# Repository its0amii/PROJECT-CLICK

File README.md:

PROJECT-CLICK

PROJECT-CLICK is a **3×2 matrix macropad** with a **cyberpunk-inspired design**, built around the **XIAO RP2040**.
I tried to make it look good as posible and it was my first build so it will have its own problems
(the case is tight fit)

## Features
3x2 matrix 
multilayered keys
knob for volume 
display

## Hackpad Overview

> *Screenshot build*

## Schematic

The schematic includes:

* 6-key matrix with individual diodes
* OLED display connection
* Rotary encoder
* RP2040-based controller

Designed using **KiCad**.

> *Screenshot of the schematic*

## PCB

I used KiCad to design my PCB and used JLCPCB to get it printed

* Cherry MX switch 

> *PCBlayout*

## Case & Assembly

the case have two part top and bottom 

* Base (holds the PCB)
* Top plate 

scrwe used in this project is **M3 screws and heatset inserts**

> *Screenshot of the case and how it fits together*

## Firmware Overview

PROJECT-CLICK is designed to run **KMK firmware**.

Planned functionality:

* 6 programmable macro keys
* Rotary encoder for volume/scrolling/custom actions(such as multilayering)
* OLED display for status and layers.

(program is not perfect or tested yet since i am new to this )

## Bill of Materials

Everything required to build one PROJECT-CLICK unit:

### Electronics

* 6× Cherry MX switches
* 6× Blank DSA keycaps
* 6× 1N4148 DO-35 diodes
* 1× 0.91" 128×32 OLED display
* 1× EC11 rotary encoder
* 1× XIAO RP2040

### Hardware

* 10× M3×5×4 heatset inserts
* 15× M3×16mm screws

### Case

* 1× Case (2 printed parts)

## Tools Used

* **KiCad**
* **Fusion 360**
* **KMK** 
* **3D Printer**

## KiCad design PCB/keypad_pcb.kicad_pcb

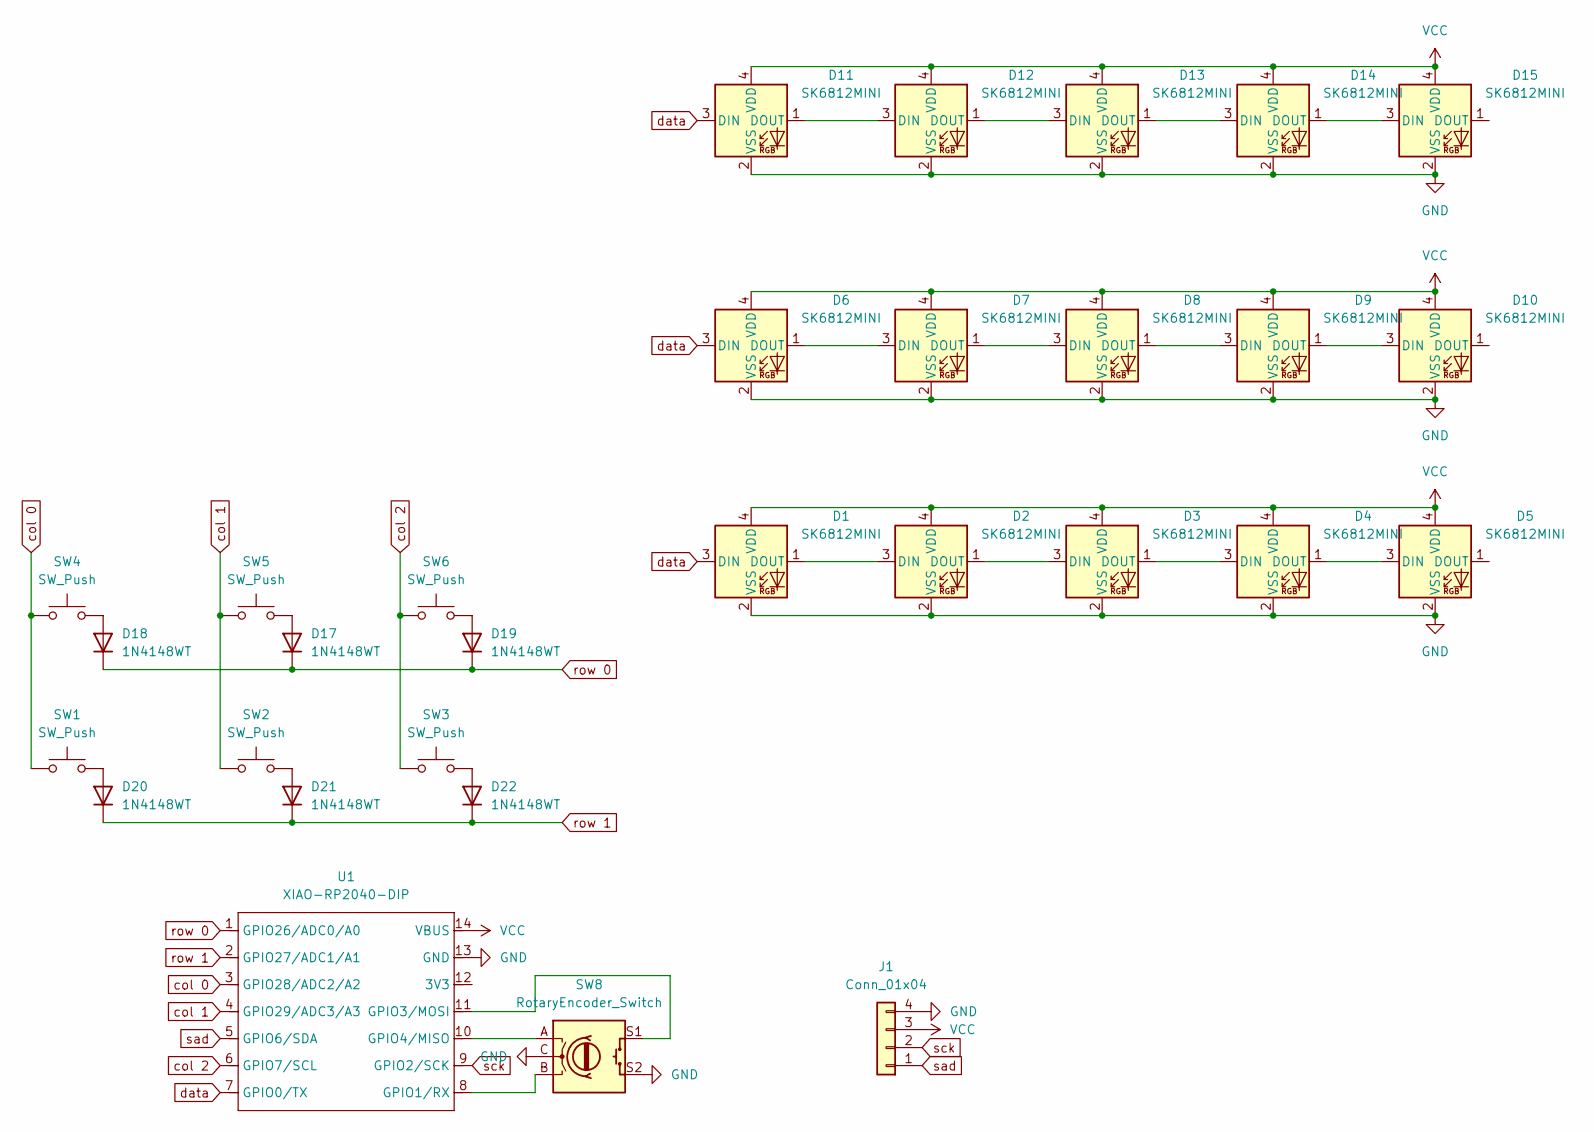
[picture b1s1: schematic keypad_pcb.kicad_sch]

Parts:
D1, D2, D3, D4, D5, D6, D7, D8, D9, D10, D11, D12, D13, D14, D15: SK6812MINI; LED_SK6812MINI_PLCC4_3.5x3.5mm_P1.75mm
D17, D18, D19, D20, D21, D22: 1N4148WT; Diode_DO-35
J1: Conn_01x04; OLED_128x32
SW1, SW2, SW3, SW4, SW5, SW6: SW_Push; SW_Cherry_MX_1.00u_PCB
SW8: RotaryEncoder_Switch; RotaryEncoder_Alps_EC11E-Switch_Vertical_H20mm
U1: XIAO-RP2040-DIP

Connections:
GND: D1.2 (VSS), D2.2 (VSS), D3.2 (VSS), D4.2 (VSS), D5.2 (VSS), D6.2 (VSS), D7.2 (VSS), D8.2 (VSS), D9.2 (VSS), D10.2 (VSS), D11.2 (VSS), D12.2 (VSS), D13.2 (VSS), D14.2 (VSS), D15.2 (VSS), J1.4, SW8.C, SW8.S2, U1.13 (GND)
unnamed: D1.1 (DOUT), D2.3 (DIN)
unnamed: D2.1 (DOUT), D3.3 (DIN)
unnamed: D3.1 (DOUT), D4.3 (DIN)
unnamed: D4.1 (DOUT), D5.3 (DIN)
unnamed: D6.1 (DOUT), D7.3 (DIN)
unnamed: D7.1 (DOUT), D8.3 (DIN)
unnamed: D8.1 (DOUT), D9.3 (DIN)
unnamed: D9.1 (DOUT), D10.3 (DIN)
unnamed: D11.1 (DOUT), D12.3 (DIN)
unnamed: D12.1 (DOUT), D13.3 (DIN)
unnamed: D13.1 (DOUT), D14.3 (DIN)
unnamed: D14.1 (DOUT), D15.3 (DIN)
unnamed: D17.2 (A), SW5.2
unnamed: D18.2 (A), SW4.2
unnamed: D19.2 (A), SW6.2
unnamed: D20.2 (A), SW1.2
unnamed: D21.2 (A), SW2.2
unnamed: D22.2 (A), SW3.2
unnamed: SW8.B, U1.8 (GPIO1/RX)
unnamed: SW8.S1, U1.11 (GPIO3/MOSI)
unnamed: SW8.A, U1.10 (GPIO4/MISO)
VCC: D1.4 (VDD), D2.4 (VDD), D3.4 (VDD), D4.4 (VDD), D5.4 (VDD), D6.4 (VDD), D7.4 (VDD), D8.4 (VDD), D9.4 (VDD), D10.4 (VDD), D11.4 (VDD), D12.4 (VDD), D13.4 (VDD), D14.4 (VDD), D15.4 (VDD), J1.3, U1.14 (VBUS)
col 0: SW1.1, SW4.1, U1.3 (GPIO28/ADC2/A2)
col 1: SW2.1, SW5.1, U1.4 (GPIO29/ADC3/A3)
col 2: SW3.1, SW6.1, U1.6 (GPIO7/SCL)
data: D1.3 (DIN), D6.3 (DIN), D11.3 (DIN), U1.7 (GPIO0/TX)
row 0: D17.1 (K), D18.1 (K), D19.1 (K), U1.1 (GPIO26/ADC0/A0)
row 1: D20.1 (K), D21.1 (K), D22.1 (K), U1.2 (GPIO27/ADC1/A1)
sad: J1.1, U1.5 (GPIO6/SDA)
sck: J1.2, U1.9 (GPIO2/SCK)

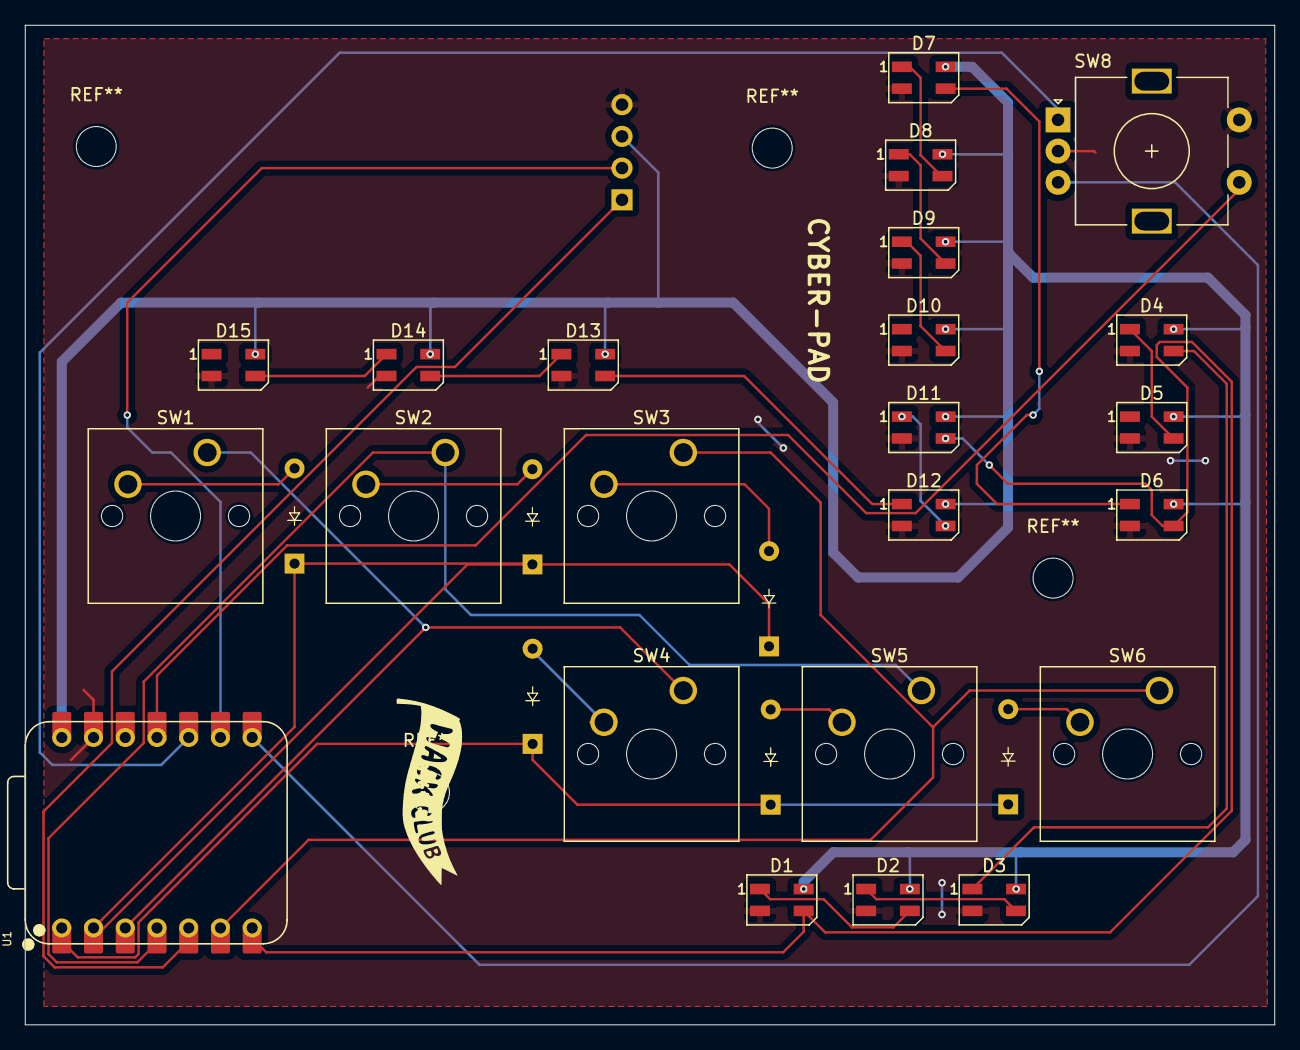
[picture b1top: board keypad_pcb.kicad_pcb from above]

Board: 2 copper layers, 100.0 x 80.0 mm, 30 parts (1 on the bottom side), 31 nets.

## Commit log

2026-01-25 PROJECT-CLICK
    PROJECT-CLICK my first marco pad
2026-01-25 PROJECT-CLICK
    PROJECT-CLICK
2026-03-22 Revise README.md with project details and improvements
    Updated README.md to include new project details and features, along with screenshots and descriptions of the schematic, PCB, case assembly, firmware overview, BOM, and tools used.
2026-03-30 case update
    i have updated case and fixed the shape
2026-03-30 case update
2026-03-30 CASE TOP
2026-03-30 Revise README for PROJECT-CLICK
    Updated README.md to improve formatting and clarity.
